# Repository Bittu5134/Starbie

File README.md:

# Starbie

A tiny motion-controlled digital pet, basically a desktop Tamagotchi. Totally not a Starboy.

## Overview

Starbie is an interactive desktop companion powered by the **Seeed Studio XIAO ESP32-C3**. It features an OLED display for animated expressions and reactions, mechanical key switches for interaction, an MPU6050 6-axis IMU for motion and tilt sensing, and a DHT11 sensor for environmental temperature/humidity monitoring.

### 3D Render

| Front | Back |
| :---: | :---: |
|  |  |

---

## Hardware Specifications

- **Microcontroller:** Seeed Studio XIAO ESP32-C3
- **Display:** 0.96" 128x64 I2C OLED (SSD1306)
- **Motion Sensor:** MPU6050 6-DoF Accelerometer & Gyroscope
- **Environment Sensor:** DHT11 Temperature & Humidity Sensor
- **Inputs:** 2x Cherry MX PCB-mount mechanical switches
- **Connectivity / Power:** USB-C (via XIAO board) / 3.3V & 5V logic

---

## Repository Structure

```text
├── firmware/
│   └── starbie/
│       └── Starbie.ino         # Arduino sketch for Starbie pet firmware
├── hardware/
│   ├── half_life_week_one.kicad_pcb   # KiCad PCB layout
│   ├── half_life_week_one.kicad_sch   # KiCad schematic
│   ├── half_life_week_one.kicad_pro   # KiCad project file
│   ├── bom.csv                        # Bill of Materials
│   ├── gerbers.zip                    # Production Gerber and drill files (zipped)
│   ├── gerbers/                       # Raw Gerber plot outputs
│   └── Imported Parts.pretty/         # Custom footprint libraries
├── images/
│   ├── pcb_front.png           # 3D render of PCB (Front)
│   └── pcb_back.png            # 3D render of PCB (Back)
├── bom.csv                     # Bill of Materials (root copy for bots)
├── BOM.md                      # Half-Life synced parts list
├── JOURNAL.md                  # Development log
└── README.md                   # Project overview & documentation
```

---

## Bill of Materials

| Reference | Component | Footprint | Quantity |
| --- | --- | --- | --- |
| **U1** | XIAO ESP32-C3 | Seeed XIAO SMD/DIP | 1 |
| **J1** | 0.96" I2C OLED (128x64) | 1x04 2.54mm Header | 1 |
| **J2** | MPU-6050 IMU Module | 1x08 2.54mm Header | 1 |
| **U2** | DHT11 Sensor | DHT11 4-Pin | 1 |
| **SW1, SW2** | Cherry MX Switches | Cherry MX 1.00u PCB | 2 |
| **R1** | 10kΩ Resistor | Axial DIN0204 Horizontal | 1 |

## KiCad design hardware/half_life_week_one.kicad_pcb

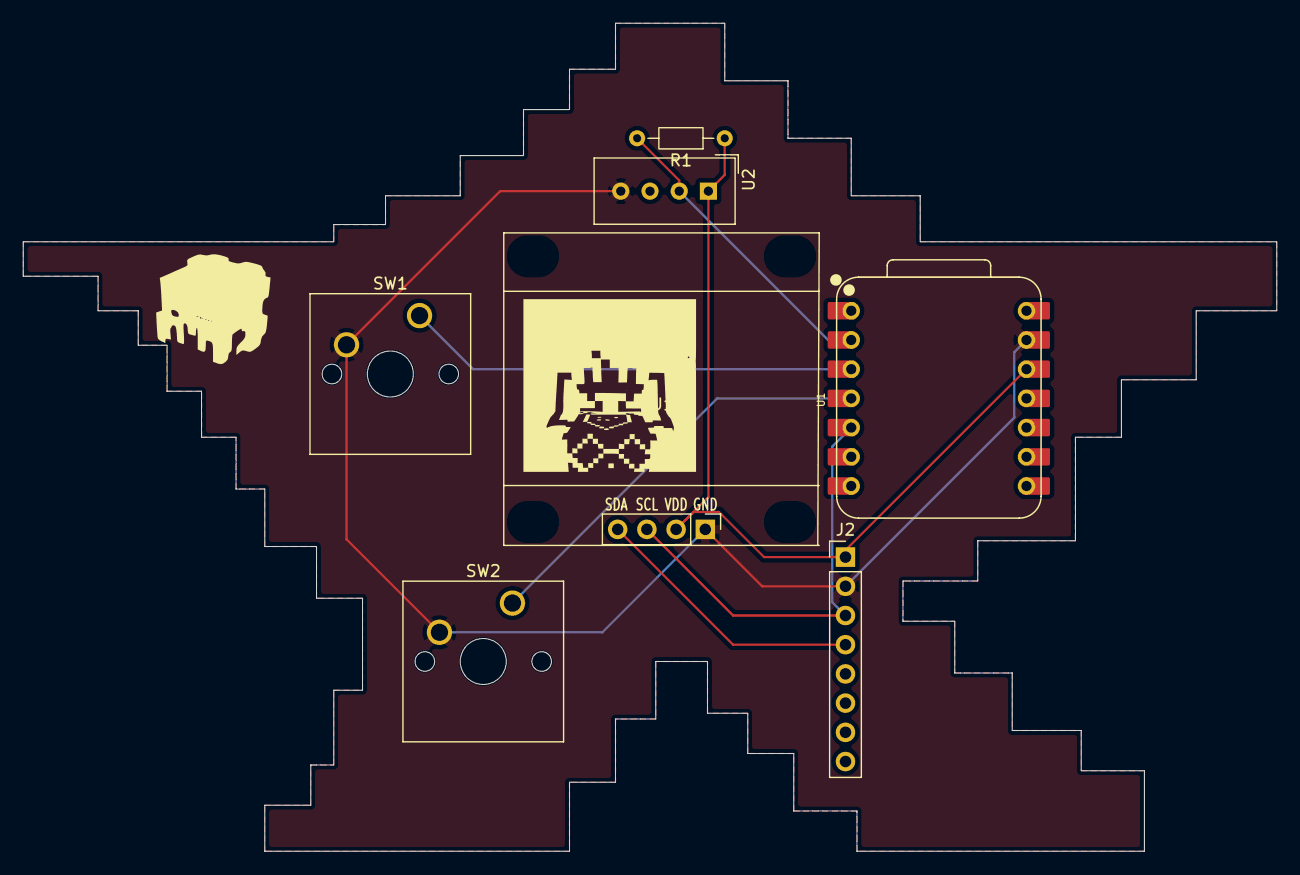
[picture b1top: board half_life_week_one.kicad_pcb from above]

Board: 2 copper layers, 109.0 x 72.0 mm, 7 parts (0 on the bottom side), 7 nets.

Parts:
J1: Conn_01x04_Pin; Display_128x64_096_I2C
J2: Conn_01x08_Pin; PinHeader_1x08_P2.54mm_Vertical
R1: 10k; R_Axial_DIN0204_L3.6mm_D1.6mm_P7.62mm_Horizontal
SW1, SW2: SW_Push; SW_Cherry_MX_1.00u_PCB
U1: XIAO-ESP32-C3-SMD; XIAO-ESP32-C6-DIP
U2: DHT11; Aosong_DHT11_5.5x12.0_P2.54mm

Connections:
+3.3V: J1.2, J2.1, R1.1, U1.12 (3V3_OUT), U2.1 (VDD)
/DHT11 DATA: R1.2, U1.2 (D1), U2.2 (DATA)
/GPIO2: SW1.1, U1.3 (D2)
/GPIO3: SW2.1, U1.4 (D3)
/SCL: J1.3, J2.3, U1.5 (D4)
/SDA: J1.4, J2.4
GND: J1.1, J2.2, SW1.2, SW2.2, U1.13 (GND), U2.4 (GND)
